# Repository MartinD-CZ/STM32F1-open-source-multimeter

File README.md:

# STM32 OpenSource Multimeter
*see the article [here](http://embedblog.eu/?p=438) or the video [here](https://youtu.be/qQX5iS70-mg)*

## Specs (revision 1.5 - latest stable)
1. voltage measurement: ±60 V, ±6 V, ±600 mV, ±60 m ranges, with DC or RMS data acquisition
2. current measurement: ±250 or ±2500 mA ranges, again with DC or RMS
3. can measure voltage and current simultaneously and display the product, ie power
4. measures continuity and displays the resistance and voltage drop
5. can perform simple component testing
6. frequency measurement up to 10 MHz

Additional features: isolated USB serial port; ; 2 kB EEPROM; 4 bit expansion port; battery voltage measurement & charging via USB; firmware update via USB; integrated kickstand; hold function

*Note: when this project started, it used STM32F1. Now it uses STM32F3, but I cannot rename the repository, so I hope it won't mislead anyone.*

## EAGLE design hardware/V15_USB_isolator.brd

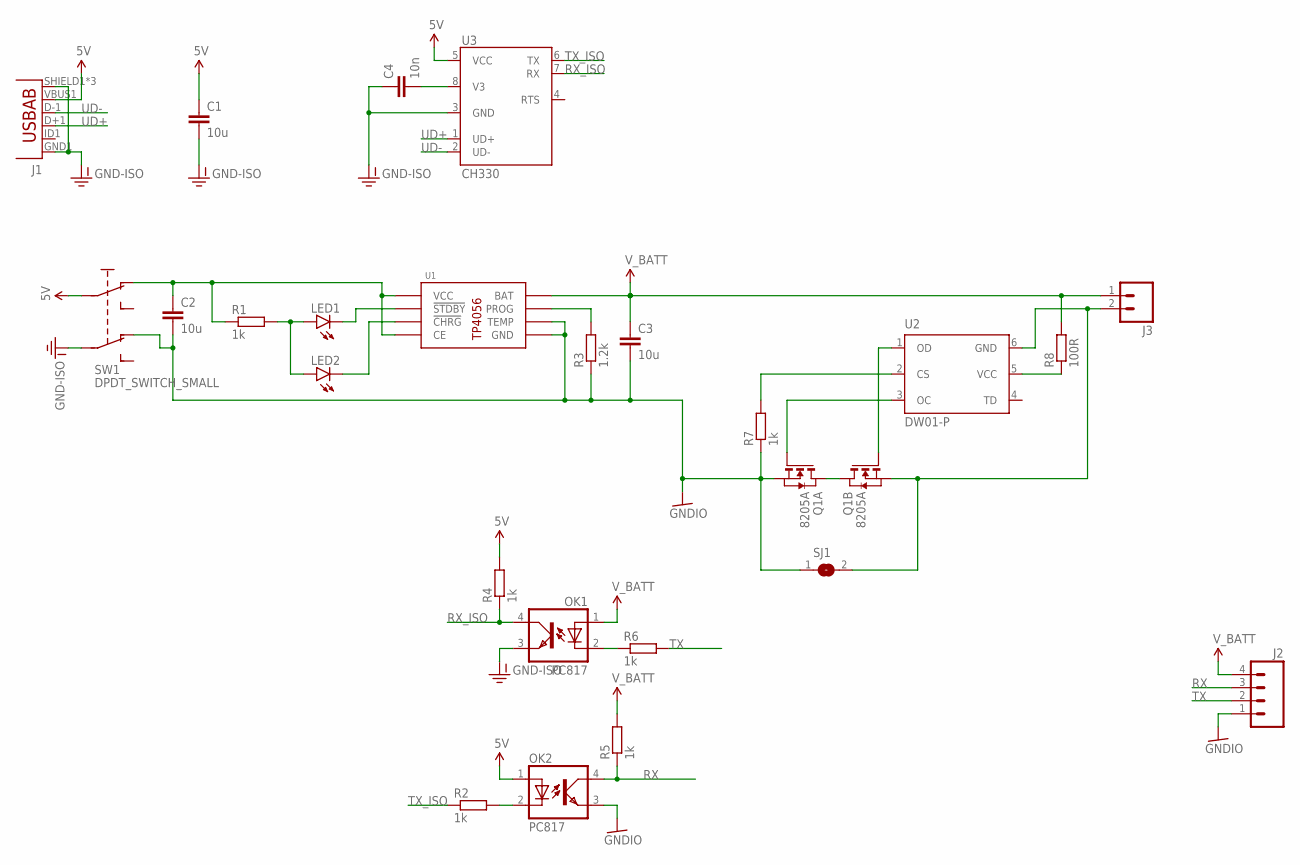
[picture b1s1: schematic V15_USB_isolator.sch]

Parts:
C1, C2, C3: 10u; C1206
C4: 10n; C1206
J1: USB-ABCONN-11794; USB-AB-MICRO-SMD_V03
J2: M04PTH; 1X04@1
J3: M02PTH3; 1X02_LONGPADS
LED1, LED2: LED1206-BOTTOM; LED-1206-BOTTOM
OK1, OK2: PC817; DIL04
Q1: 8205A; TSSOP8
R1, R2, R4, R5, R6, R7: 1k; R1206
R3: 1.2k; R1206
R8: 100R; R1206
SJ1: SJ
SW1: DPDT_SWITCH_SMALL; DPDT_SMALL
U1: TP4056; SOP8
U2: DW01-P; SOT23-6L
U3: CH330; SO08

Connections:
5V: C1.1, J1.VBUS1 (VBUS), OK2.1 (A), R4.2, SW1.P$2 (I1), U3.5 (VCC)
5V_ISO: C2.1, R1.1, SW1.P$1 (NC1), U1.4 (VCC), U1.8 (CE)
GND-ISO: C1.2, C4.1, J1.GND1 (GND), J1.SHIELD1 (SHIELD), J1.SHIELD2 (SHIELD), J1.SHIELD3 (SHIELD), OK1.3 (EMIT), SW1.P$5 (I2), U3.3 (GND)
GNDIO: C2.2, C3.2, J2.1, OK2.3 (EMIT), Q1.2 (S), Q1.3 (S), R3.1, R7.1, SJ1.1, SW1.P$6 (NC2), U1.1 (TEMP), U1.3 (GND)
unnamed: C4.2, U3.8 (V3)
unnamed: Q1.1 (D), Q1.8 (D)
unnamed: LED1.A, LED2.A, R1.2
unnamed: LED1.C, U1.6 (!STDBY)
unnamed: LED2.C, U1.7 (!CHRG)
unnamed: R3.2, U1.2 (PROG)
unnamed: OK2.2 (C), R2.2
unnamed: OK1.2 (C), R6.1
unnamed: R8.1, U2.5 (VCC)
unnamed: J3.2, Q1.6 (S), Q1.7 (S), SJ1.2, U2.6 (GND)
unnamed: Q1.5 (G), U2.1 (OD)
unnamed: Q1.4 (G), U2.3 (OC)
unnamed: R7.2, U2.2 (CS)
RX: J2.3, OK2.4 (COL), R5.1
RX_ISO: OK1.4 (COL), R4.1, U3.7 (RX)
TX: J2.2, R6.2
TX_ISO: R2.1, U3.6 (TX)
UD+: J1.D+1 (D+), U3.1 (UD+)
UD-: J1.D-1 (D-), U3.2 (UD-)
V_BATT: C3.1, J2.4, J3.1, OK1.1 (A), R5.2, R8.2, U1.5 (BAT)

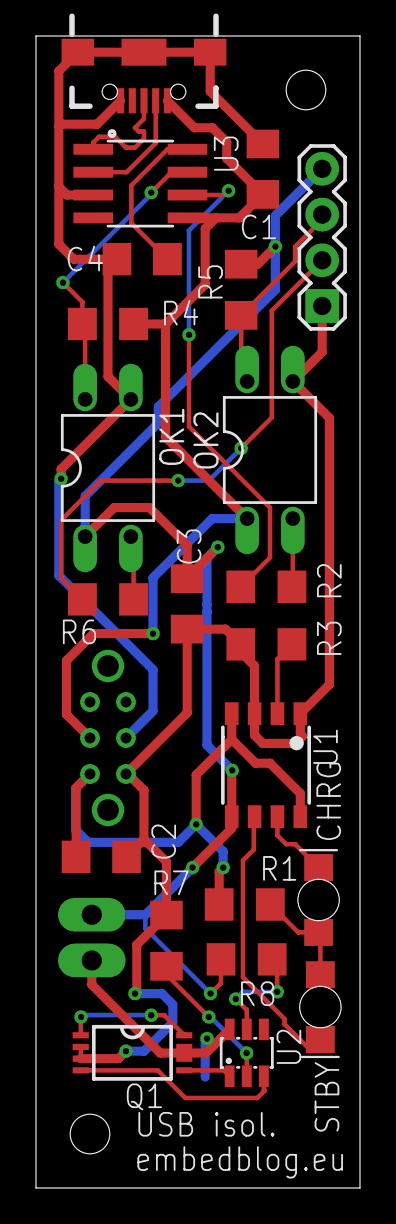
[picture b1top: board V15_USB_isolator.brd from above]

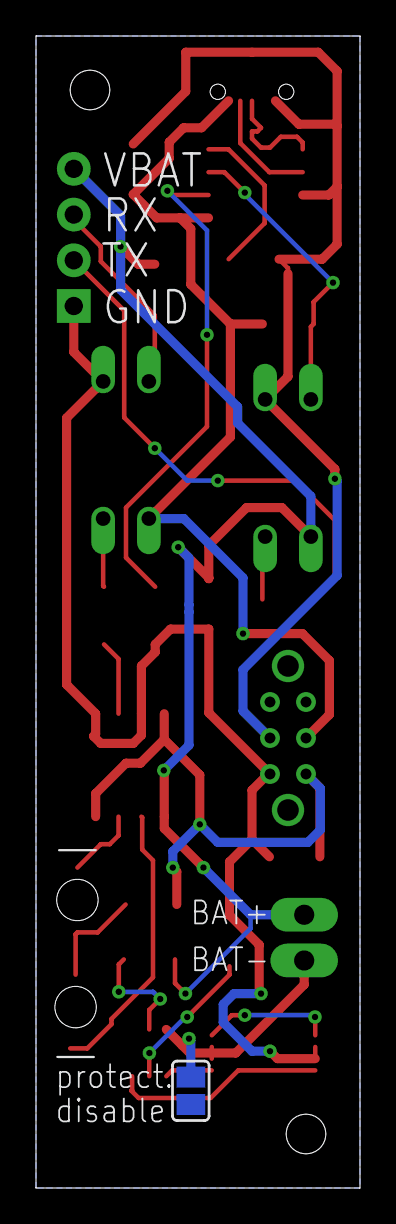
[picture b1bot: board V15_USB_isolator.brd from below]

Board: 2 copper layers, 18.0 x 64.0 mm, 25 parts (2 on the bottom side), 24 nets.

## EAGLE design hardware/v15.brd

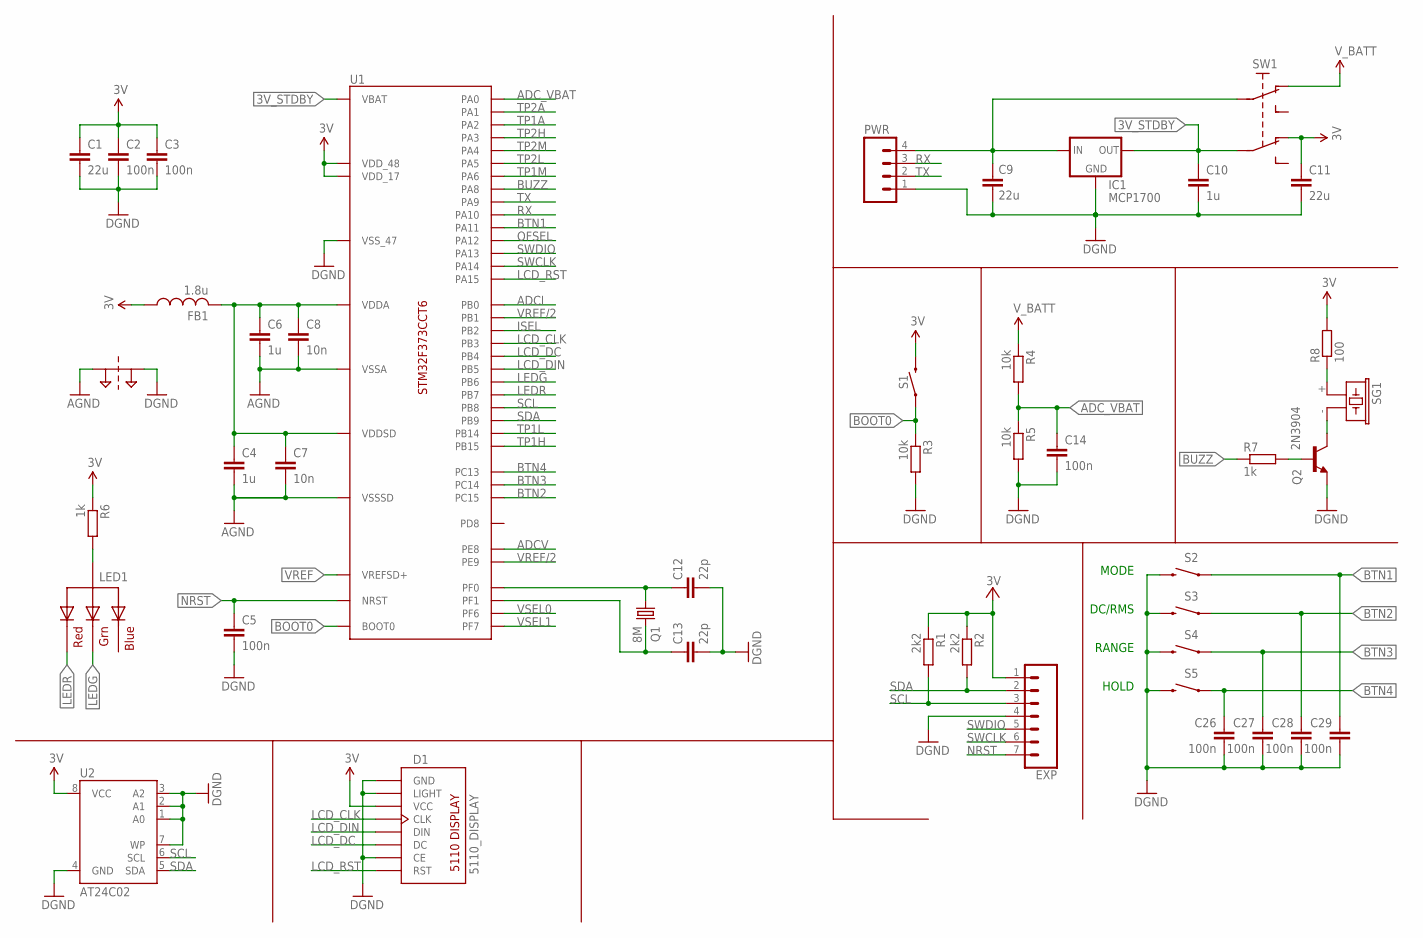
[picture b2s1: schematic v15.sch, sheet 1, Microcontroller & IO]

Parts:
C1, C9, C11: 22u; C1206
C2, C3, C5, C14, C26, C27, C28, C29: 100n; C1206
C4, C6, C10: 1u; C1206
C7, C8: 10n; C1206
C12, C13: 22p; C1206
D1: 5110_DISPLAY; 5110_LAYOUT
EXP: CONN_07; 1X07
FB1: 1.8u; 1206
IC1: MCP1700; SOT23
LED1: RGBLED_CA-5MM; LED5MMRGB
PT1: 2PT_GND_TIE
PWR: M04PTH; 1X04@1
Q1: 8M; HC49U-V
Q2: 2N3904; SOT23
R1, R2: 2k2; R1206
R3, R4, R5: 10k; R1206
R6, R7: 1k; R1206
R8: 100; R1206
S1: MOMENTARY-SWITCH-SPST-PTH-6.0MM; TACTILE_SWITCH_PTH_6.0MM
S2, S3, S4, S5: MOMENTARY-SWITCH-SPST-SMD-12MM; TACTILE_SWITCH_SMD_12MM
SG1: F/CM12P
SW1: DPDT_SWITCH_SMALL; DPDT_SMALL
U1: STM32F373CCT6; LQFP-48
U2: AT24C02; SOIC8

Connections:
3V: C1.1, C2.1, C3.1, C11.1, D1.VCC, EXP.1, FB1.1, R1.1, R2.1, R6.1, R8.2, S1.3 (2), SW1.P$6 (NC2), U1.17 (VDD_17), U1.48 (VDD_48), U2.8 (VCC); also elsewhere on the board
3V_STDBY: C10.1, IC1.2 (OUT), SW1.P$5 (I2), U1.1 (VBAT)
ADCI: U1.18 (PB0); also elsewhere on the board
ADCV: U1.21 (PE8); also elsewhere on the board
ADC_VBAT: C14.1, R4.2, R5.1, U1.10 (PA0)
AGND: C4.2, C6.2, C7.2, C8.2, PT1.P$1, U1.8 (VSSA), U1.23 (VSSSD); also elsewhere on the board
BOOT0: R3.1, S1.1, U1.44 (BOOT0)
BTN1: C29.1, S2.1, U1.32 (PA11)
BTN2: C28.1, S3.1, U1.4 (PC15)
BTN3: C27.1, S4.1, U1.3 (PC14)
BTN4: C26.1, S5.1, U1.2 (PC13)
BUZZ: R7.1, U1.29 (PA8)
GND: C1.2, C2.2, C3.2, C5.2, C9.2, C10.2, C11.2, C12.2, C13.2, C14.2, C26.2, C27.2, C28.2, C29.2, D1.CE, D1.GND, D1.LIGHT, EXP.4, IC1.1 (GND), PT1.P$2, PWR.1, Q2.2 (E), R3.2, R5.2, S2.3 (2), S3.3 (2), S4.3 (2), S5.3 (2), U1.47 (VSS_47), U2.1 (A0), U2.2 (A1), U2.3 (A2), U2.4 (GND), U2.7 (WP)
ISEL: U1.20 (PB2); also elsewhere on the board
LCD_CLK: D1.CLK, U1.39 (PB3)
LCD_DC: D1.DC, U1.40 (PB4)
LCD_DIN: D1.DIN, U1.41 (PB5)
LCD_RST: D1.RST, U1.38 (PA15)
LEDG: LED1.3 (GREEN), U1.42 (PB6)
LEDR: LED1.1 (RED), U1.43 (PB7)
unnamed: C12.1, Q1.1, U1.5 (PF0)
unnamed: C4.1, C6.1, C7.1, C8.1, FB1.2, U1.9 (VDDA), U1.24 (VDDSD)
unnamed: C9.1, IC1.3 (IN), PWR.4, SW1.P$2 (I1)
unnamed: LED1.2 (VCC), R6.2
unnamed: R8.1, SG1.+ (1)
unnamed: C13.1, Q1.2, U1.6 (PF1)
unnamed: Q2.3 (C), SG1.- (2)
unnamed: Q2.1 (B), R7.2
NRST: C5.1, EXP.7, U1.7 (NRST)
OFSEL: U1.33 (PA12); also elsewhere on the board
RX: PWR.3, U1.31 (PA10)
SCL: EXP.3, R1.2, U1.45 (PB8), U2.6 (SCL)
SDA: EXP.2, R2.2, U1.46 (PB9), U2.5 (SDA)
SWCLK: EXP.6, U1.37 (PA14)
SWDIO: EXP.5, U1.34 (PA13)
TP1A: U1.12 (PA2); also elsewhere on the board
TP1H: U1.27 (PB15); also elsewhere on the board
TP1L: U1.26 (PB14); also elsewhere on the board
TP1M: U1.16 (PA6); also elsewhere on the board
TP2A: U1.11 (PA1); also elsewhere on the board
TP2H: U1.13 (PA3); also elsewhere on the board
TP2L: U1.15 (PA5); also elsewhere on the board
TP2M: U1.14 (PA4); also elsewhere on the board
TX: PWR.2, U1.30 (PA9)
VREF: U1.25 (VREFSD+); also elsewhere on the board
VREF/2: U1.19 (PB1), U1.22 (PE9); also elsewhere on the board
VSEL0: U1.35 (PF6); also elsewhere on the board
VSEL1: U1.36 (PF7); also elsewhere on the board
V_BATT: R4.1, SW1.P$1 (NC1)

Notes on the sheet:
MODE
RANGE
DC/RMS
HOLD

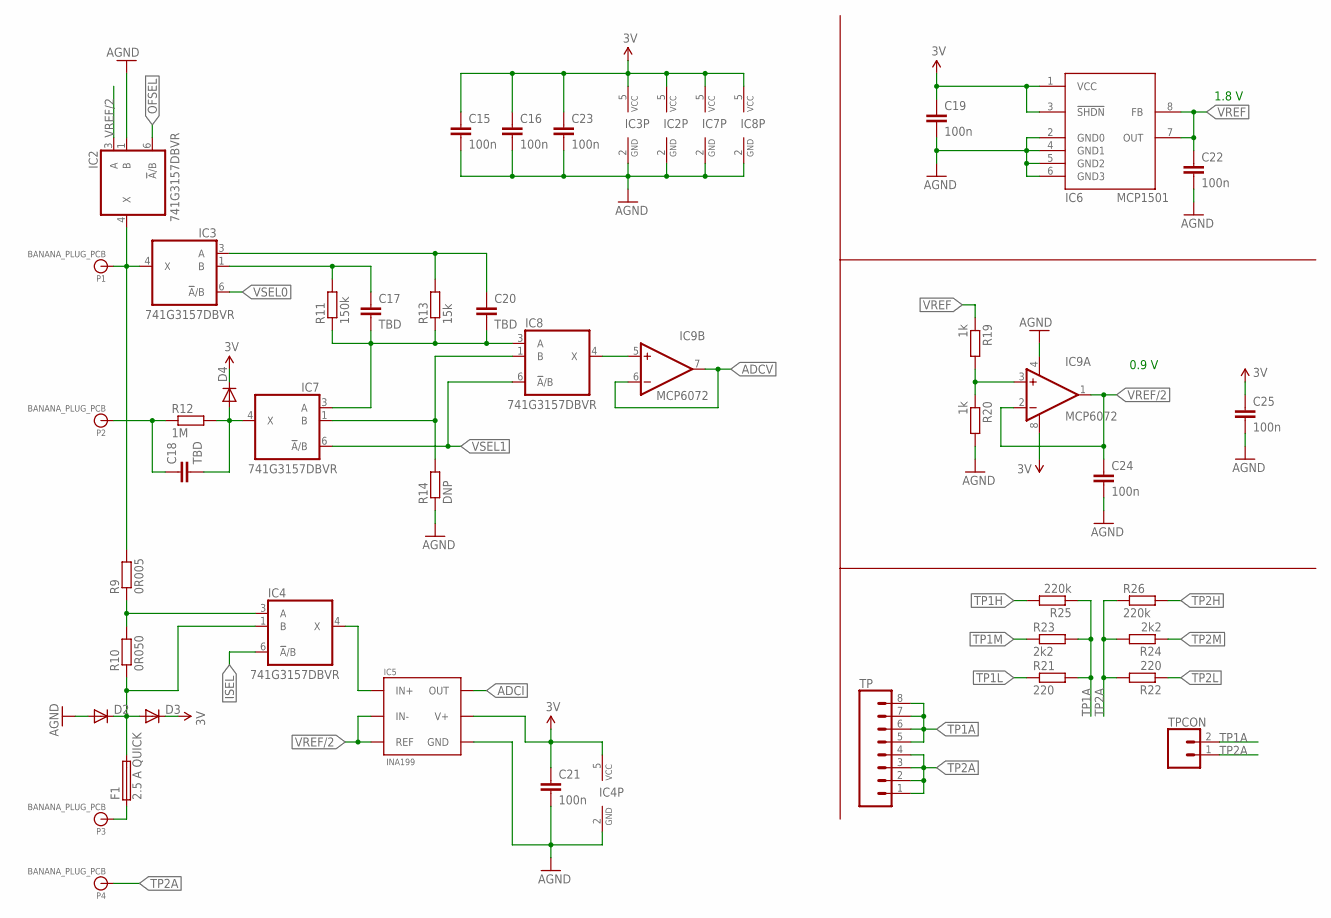
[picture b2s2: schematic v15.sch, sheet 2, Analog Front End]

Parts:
C15, C16, C21, C23: 100n; 1206
C17, C18, C20: TBD; 1206
C19, C22, C24, C25: 100n; C1206
D2, D3, D4: DIODE-MINIMELF; MINIMELF
F1: 2.5 A QUICK; SHK20L
IC2, IC3, IC4, IC7, IC8: 741G3157DBVR; DBV_R-PDSO-G6
IC5: INA199; SC70-6
IC6: MCP1501; SO08
IC9: MCP6072; SO08
P1, P2, P3, P4: BANANA_PLUG_PCB; BANANA_6MMHOLE
R9: 0R005; R1206
R10: 0R050; R1206
R11: 150k; R1206
R12: 1M; R1206
R13: 15k; R1206
R14: DNP; R1206
R19, R20: 1k; R1206
R21, R22: 220; R1206
R23, R24: 2k2; R1206
R25, R26: 220k; R1206
TP: CONN_08SMD-STRAIGHT-FEMALE; 1X08_SMD
TPCON: CONN_02; 1X02

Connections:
3V: C15.1, C16.1, C19.1, C21.1, C23.1, C25.1, D3.C, D4.C, IC2.5 (VCC), IC3.5 (VCC), IC4.5 (VCC), IC5.3 (V+), IC6.1 (VCC), IC6.3 (!SHDN), IC7.5 (VCC), IC8.5 (VCC), IC9.8 (V+); also elsewhere on the board
ADCI: IC5.6 (OUT); also elsewhere on the board
ADCV: IC9.6 (-IN), IC9.7 (OUT); also elsewhere on the board
AGND: C15.2, C16.2, C19.2, C21.2, C22.2, C23.2, C24.2, C25.2, D2.A, IC2.1 (B), IC2.2 (GND), IC3.2 (GND), IC4.2 (GND), IC5.2 (GND), IC6.2 (GND0), IC6.4 (GND1), IC6.5 (GND2), IC6.6 (GND3), IC7.2 (GND), IC8.2 (GND), IC9.4 (V-), R14.1, R20.2; also elsewhere on the board
COM: IC2.4 (X), IC3.4 (X), P1.P$1, R9.2
ISEL: IC4.6 (!A!/B); also elsewhere on the board
unnamed: C18.1, P2.P$1, R12.1
unnamed: C17.1, IC3.1 (B), R11.2
unnamed: C20.1, IC3.3 (A), R13.2
unnamed: C18.2, D4.A, IC7.4 (X), R12.2
unnamed: IC4.3 (A), R9.1, R10.2
unnamed: C17.2, C20.2, IC7.3 (A), IC8.3 (A), R11.1, R13.1
unnamed: D2.C, D3.A, F1.2A (2), IC4.1 (B), R10.1
unnamed: IC8.4 (X), IC9.5 (+IN)
unnamed: IC7.1 (B), IC8.1 (B), R14.2
unnamed: IC9.3 (+IN), R19.2, R20.1
unnamed: IC4.4 (X), IC5.4 (IN+)
unnamed: F1.1A (1), P3.P$1
OFSEL: IC2.6 (!A!/B); also elsewhere on the board
TP1A: R21.2, R23.2, R25.1, TP.5, TP.6, TP.7, TP.8, TPCON.2; also elsewhere on the board
TP1H: R25.2; also elsewhere on the board
TP1L: R21.1; also elsewhere on the board
TP1M: R23.1; also elsewhere on the board
TP2A: P4.P$1, R22.2, R24.2, R26.1, TP.1, TP.2, TP.3, TP.4, TPCON.1; also elsewhere on the board
TP2H: R26.2; also elsewhere on the board
TP2L: R22.1; also elsewhere on the board
TP2M: R24.1; also elsewhere on the board
VREF: C22.1, IC6.7 (OUT), IC6.8 (FB), R19.1; also elsewhere on the board
VREF/2: C24.1, IC2.3 (A), IC5.1 (REF), IC5.5 (IN-), IC9.1 (OUT), IC9.2 (-IN); also elsewhere on the board
VSEL0: IC3.6 (!A!/B); also elsewhere on the board
VSEL1: IC7.6 (!A!/B), IC8.6 (!A!/B); also elsewhere on the board

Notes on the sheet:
1.8 V
0.9 V

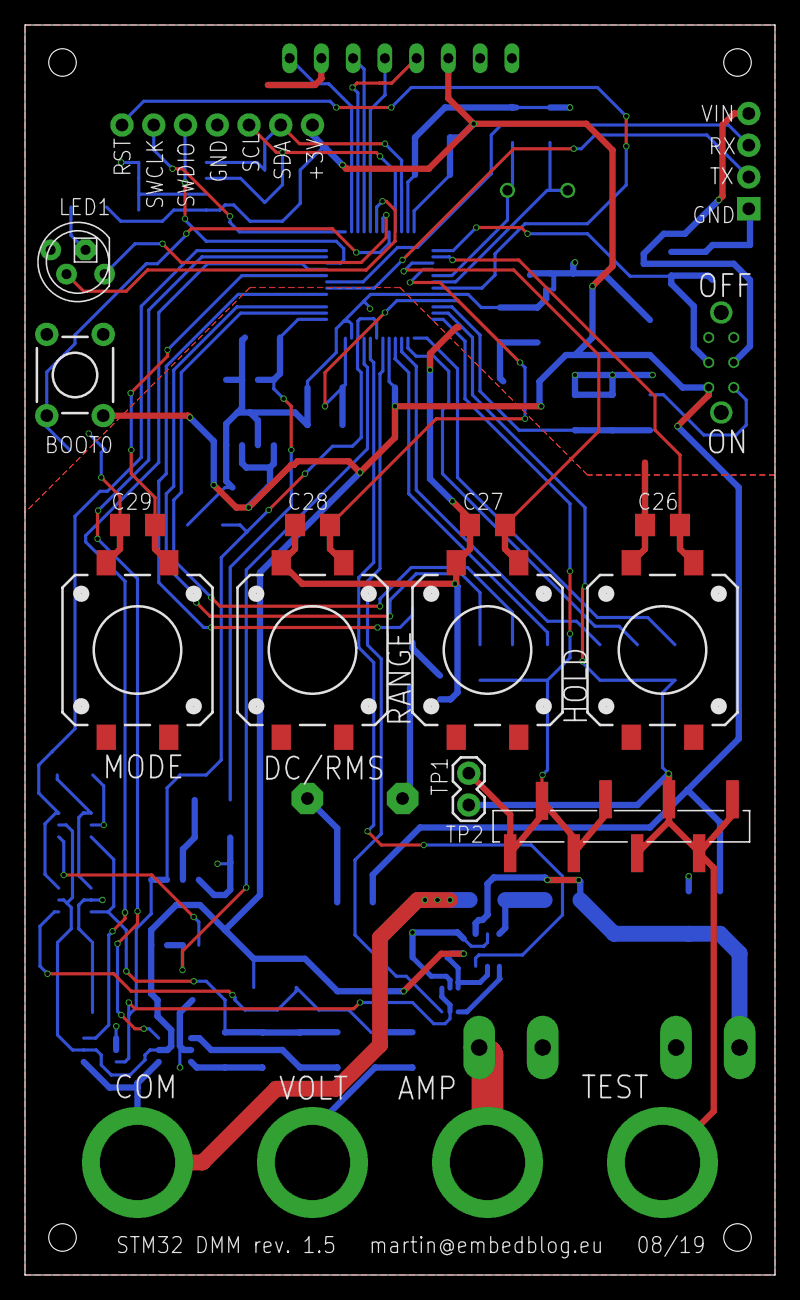
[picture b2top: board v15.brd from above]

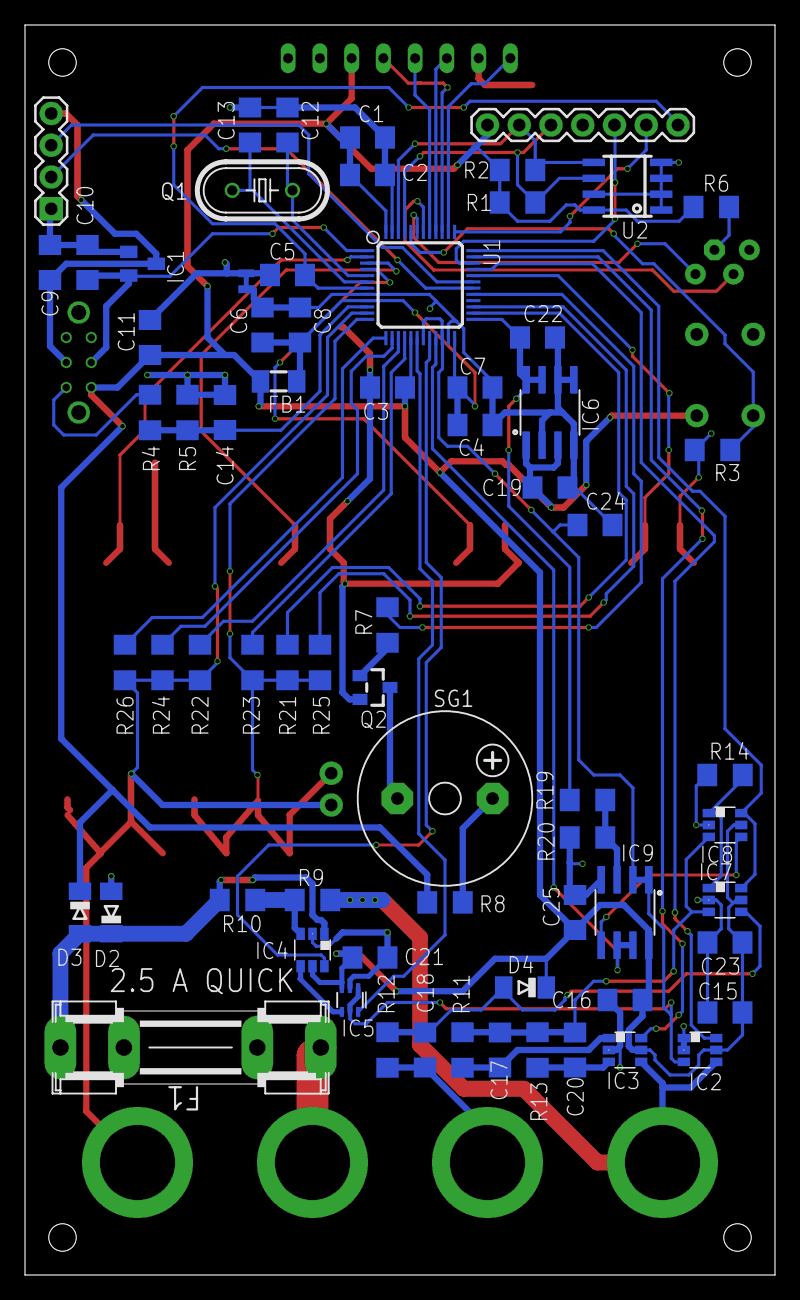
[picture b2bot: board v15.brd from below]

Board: 2 copper layers, 60.0 x 100.0 mm, 87 parts (69 on the bottom side), 62 nets.

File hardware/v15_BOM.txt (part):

Part  Value                           Device                          Package                  Description                                                                                                     MF MPN OC_FARNELL OC_NEWARK PROD_ID     SF_ID     SF_SKU   
C1    22u                             C-EUC1206                       C1206                    CAPACITOR, European symbol                                                                                                                                                 
C2    100n                            C-EUC1206                       C1206                    CAPACITOR, European symbol                                                                                                                                                 
C3    100n                            C-EUC1206                       C1206                    CAPACITOR, European symbol                                                                                                                                                 
C4    1u                              C-EUC1206                       C1206                    CAPACITOR, European symbol                                                                                                                                                 
C5    100n                            C-EUC1206                       C1206                    CAPACITOR, European symbol                                                                                                                                                 
C6    1u                              C-EUC1206                       C1206                    CAPACITOR, European symbol                                                                                                                                                 
C7    10n                             C-EUC1206                       C1206                    CAPACITOR, European symbol                                                                                                                                                 
C8    10n                             C-EUC1206                       C1206                    CAPACITOR, European symbol                                                                                                                                                 
C9    22u                             C-EUC1206                       C1206                    CAPACITOR, European symbol                                                                                                                                                 
C10   1u                              C-EUC1206                       C1206                    CAPACITOR, European symbol                                                                                                                                                 
C11   22u                             C-EUC1206                       C1206                    CAPACITOR, European symbol                                                                                                                                                 
C12   22p                             C-EUC1206                       C1206                    CAPACITOR, European symbol                                                                                                                                                 
C13   22p                             C-EUC1206                       C1206                    CAPACITOR, European symbol                                                                                                                                                 
C14   100n                            C-EUC1206                       C1206                    CAPACITOR, European symbol                                                                                                                                                 
C15   100n                            CAP1206                         1206                     Capacitor                                                                                                                                                                  
C16   100n                            CAP1206                         1206                     Capacitor                                                                                                                                                                  
C17   TBD                             CAP1206                         1206                     Capacitor                                                                                                                                                                  
C18   TBD                             CAP1206                         1206                     Capacitor                                                                                                                                                                  
C19   100n                            C-EUC1206                       C1206                    CAPACITOR, European symbol                                                                                                                                                 
C20   TBD                             CAP1206                         1206                     Capacitor                                                                                                                                                                  
C21   100n                            CAP1206                         1206                     Capacitor                                                                                                                                                                  
C22   100n                            C-EUC1206                       C1206                    CAPACITOR, European symbol                                                                                                                                                 
C23   100n                            CAP1206                         1206                     Capacitor                                                                                                                                                                  
C24   100n                            C-EUC1206                       C1206                    CAPACITOR, European symbol                                                                                                                                                 
C25   100n                            C-EUC1206                       C1206                    CAPACITOR, European symbol                                                                                                                                                 
C26   100n                            C-EUC1206                       C1206                    CAPACITOR, European symbol                                                                                                                                                 
C27   100n                            C-EUC1206                       C1206                    CAPACITOR, European symbol                                                                                                                                                 
C28   100n                            C-EUC1206                       C1206                    CAPACITOR, European symbol                                                                                                                                                 
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
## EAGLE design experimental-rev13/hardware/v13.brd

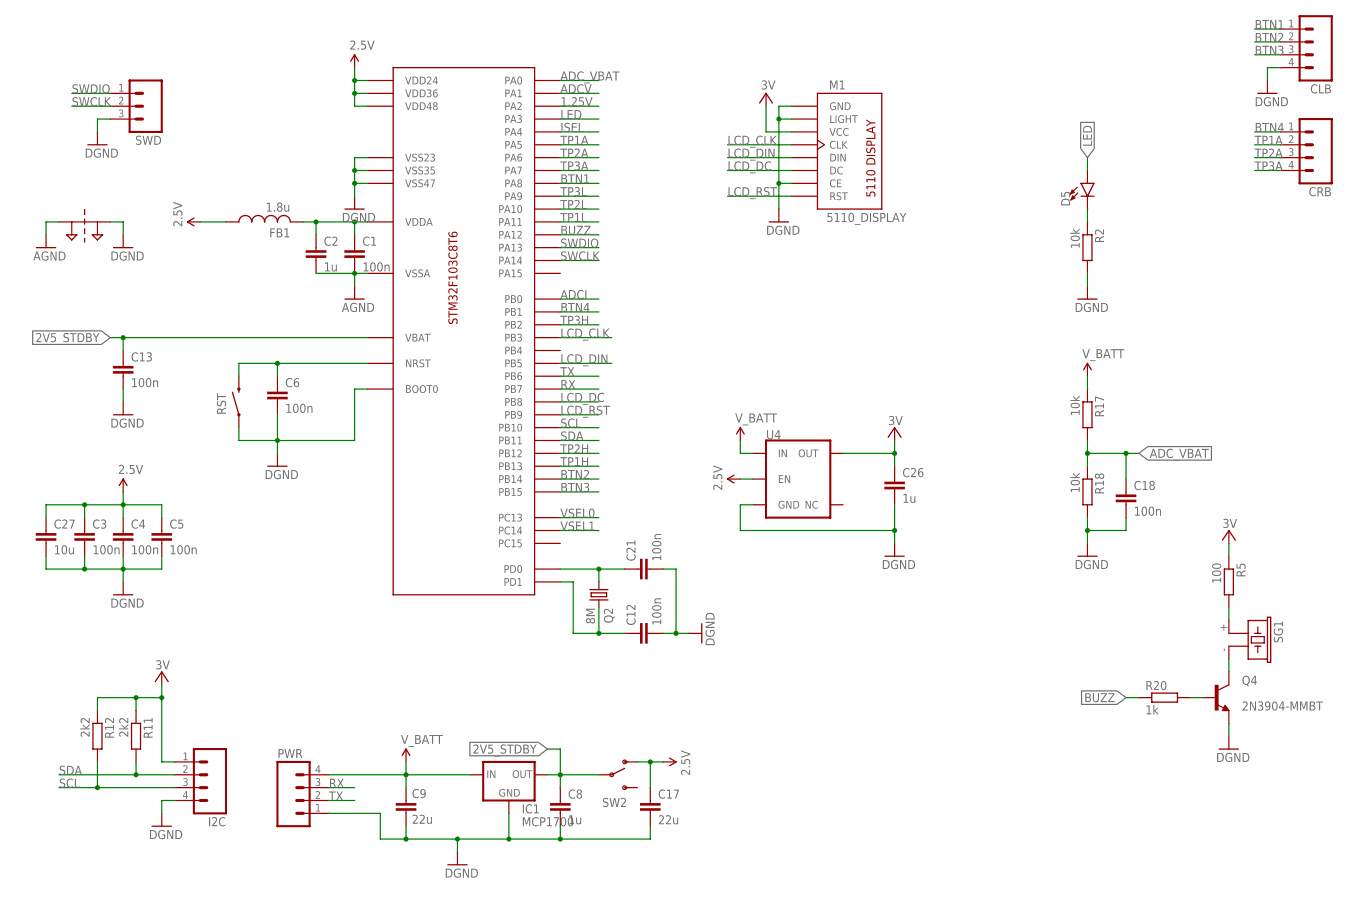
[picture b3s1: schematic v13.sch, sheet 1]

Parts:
C1, C3, C4, C5, C6, C12, C13, C18, C21: 100n; C1206
C2, C8, C26: 1u; C1206
C9, C17: 22u; C1206
C27: 10u; C1206
CLB: M04PTH; 1X04@1
CRB: M04PTH; 1X04@1
D5: LED1206; LED-1206
FB1: 1.8u; 1206
I2C: M04PTH; 1X04@1
IC1: MCP1700; SOT23
M1: 5110_DISPLAY; 5110_LAYOUT
PWR: M04PTH; 1X04@1
Q2: 8M; HC49U-V
Q4: 2N3904-MMBT; SOT23
R2, R17, R18: 10k; R1206
R5: 100; R1206
R11, R12: 2k2; R1206
R20: 1k; R1206
RST: SWITCH-MOMENTARY-2SMD; TACTILE-SWITCH-SMD
SG1: F/CM12P
SJ1: 2PT_GND_TIE
SW2: SK-12D07; SK12SWITCH
SWD: M03PTH; 1X03
U4: 3.3V; SOT23-5
U$1: STM32F103C8T6; TQFP-48

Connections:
1.25V: U$1.12 (PA2); also elsewhere on the board
2.5V: C3.1, C4.1, C5.1, C17.1, C27.1, FB1.1, SW2.IN (O), U4.3 (EN), U$1.24 (VDD24), U$1.36 (VDD36), U$1.48 (VDD48); also elsewhere on the board
2V5_STDBY: C8.1, C13.1, IC1.2 (OUT), SW2.P1, U$1.1 (VBAT)
3V: C26.1, I2C.1, M1.VCC, R5.1, R11.1, R12.1, U4.5 (OUT); also elsewhere on the board
ADCI: U$1.18 (PB0); also elsewhere on the board
ADCV: U$1.11 (PA1); also elsewhere on the board
ADC_VBAT: C18.1, R17.2, R18.1, U$1.10 (PA0)
AGND: C1.2, C2.2, SJ1.P$1, U$1.8 (VSSA); also elsewhere on the board
BTN1: CLB.1, U$1.29 (PA8)
BTN2: CLB.2, U$1.27 (PB14)
BTN3: CLB.3, U$1.28 (PB15)
BTN4: CRB.1, U$1.19 (PB1)
BUZZ: R20.1, U$1.33 (PA12)
GND: C3.2, C4.2, C5.2, C6.2, C8.2, C9.2, C12.2, C13.2, C17.2, C18.2, C21.2, C26.2, C27.2, CLB.4, I2C.4, IC1.1 (GND), M1.CE, M1.GND, M1.LIGHT, PWR.1, Q4.2 (E), R2.2, R18.2, RST.1, SJ1.P$2, SWD.3, U4.2 (GND), U$1.23 (VSS23), U$1.35 (VSS35), U$1.44 (BOOT0), U$1.47 (VSS47); also elsewhere on the board
ISEL: U$1.14 (PA4); also elsewhere on the board
LCD_CLK: M1.CLK, U$1.39 (PB3)
LCD_DC: M1.DC, U$1.45 (PB8)
LCD_DIN: M1.DIN, U$1.41 (PB5)
LCD_RST: M1.RST, U$1.46 (PB9)
LED: D5.A, U$1.13 (PA3)
unnamed: C6.1, RST.3 (2), U$1.7 (NRST)
unnamed: C21.1, Q2.1, U$1.5 (PD0)
unnamed: C1.1, C2.1, FB1.2, U$1.9 (VDDA)
unnamed: D5.C, R2.1
unnamed: R5.2, SG1.+ (1)
unnamed: C12.1, Q2.2, U$1.6 (PD1)
unnamed: Q4.3 (C), SG1.- (2)
unnamed: Q4.1 (B), R20.2
RX: PWR.3, U$1.43 (PB7)
SCL: I2C.3, R12.2, U$1.21 (PB10)
SDA: I2C.2, R11.2, U$1.22 (PB11)
SWCLK: SWD.2, U$1.37 (PA14)
SWDIO: SWD.1, U$1.34 (PA13)
TP1A: CRB.2, U$1.15 (PA5); also elsewhere on the board
TP1H: U$1.26 (PB13); also elsewhere on the board
TP1L: U$1.32 (PA11); also elsewhere on the board
TP2A: CRB.3, U$1.16 (PA6); also elsewhere on the board
TP2H: U$1.25 (PB12); also elsewhere on the board
TP2L: U$1.31 (PA10); also elsewhere on the board
TP3A: CRB.4, U$1.17 (PA7); also elsewhere on the board
TP3H: U$1.20 (PB2); also elsewhere on the board
TP3L: U$1.30 (PA9); also elsewhere on the board
TX: PWR.2, U$1.42 (PB6)
VSEL0: U$1.2 (PC13); also elsewhere on the board
VSEL1: U$1.3 (PC14); also elsewhere on the board
V_BATT: C9.1, IC1.3 (IN), PWR.4, R17.1, U4.1 (IN); also elsewhere on the board

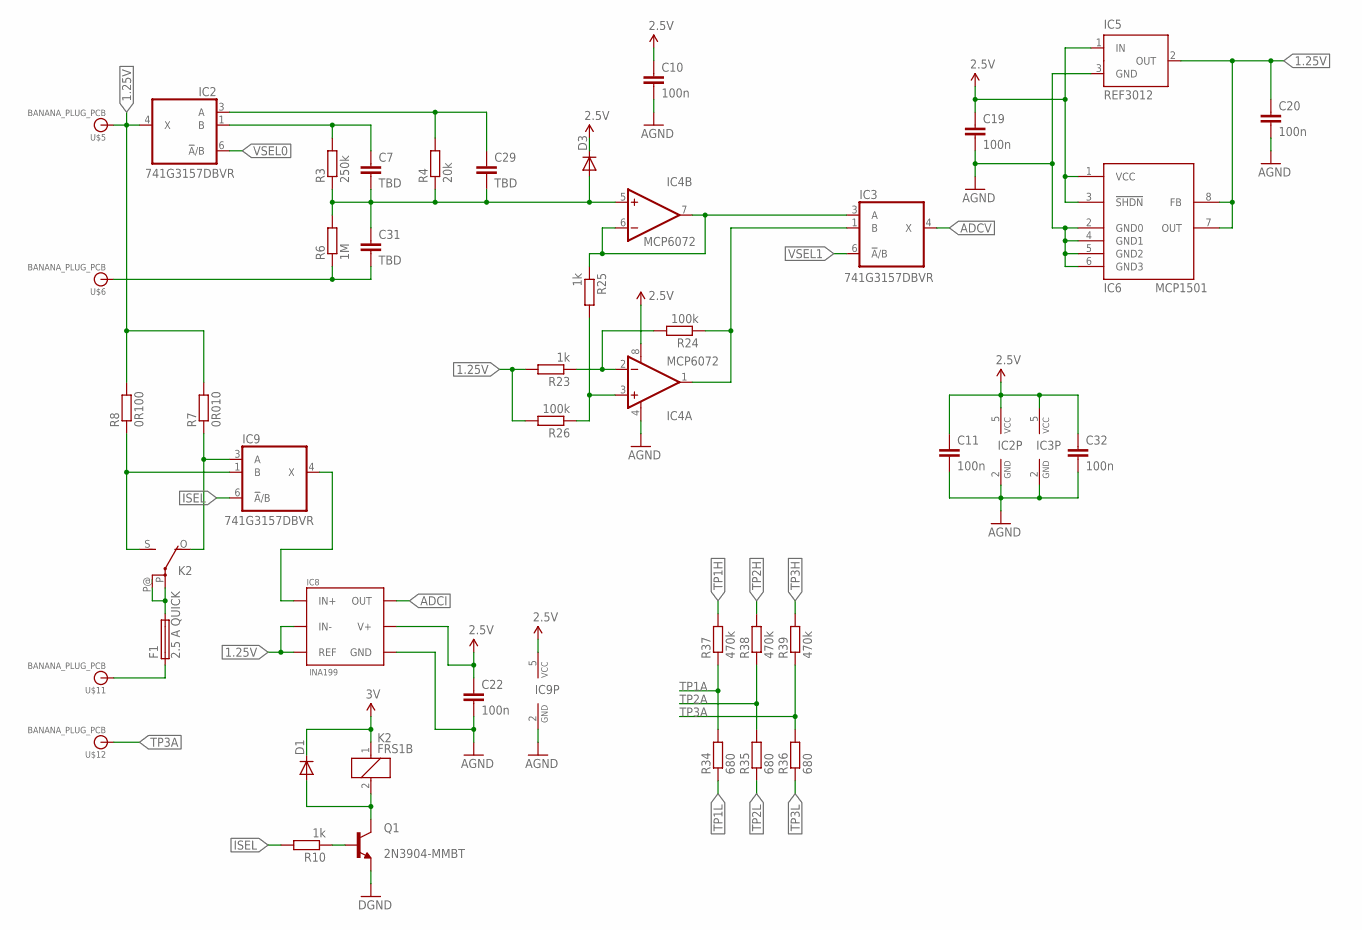
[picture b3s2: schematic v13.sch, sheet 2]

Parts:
C7, C29, C31: TBD; 1206
C10, C11, C22, C32: 100n; 1206
C19, C20: 100n; C1206
D1, D3: DIODE-MINIMELF; MINIMELF
F1: 2.5 A QUICK; SHK20L
IC2, IC3, IC9: 741G3157DBVR; DBV_R-PDSO-G6
IC4: MCP6072; SO08
IC5: REF3012; SOT23
IC6: MCP1501; SO08
IC8: INA199; SC70-6
K2: FRS1B
Q1: 2N3904-MMBT; SOT23
R3: 250k; R1206
R4: 20k; R1206
R6: 1M; R1206
R7: 0R010; R1206
R8: 0R100; R1206
R10, R23, R25: 1k; R1206
R24, R26: 100k; R1206
R34, R35, R36: 680; R1206
R37, R38, R39: 470k; R1206
U$5, U$6, U$11, U$12: BANANA_PLUG_PCB; BANANA_6MMHOLE

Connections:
1.25V: C20.1, IC2.4 (X), IC5.2 (OUT), IC6.7 (OUT), IC6.8 (FB), IC8.1 (REF), IC8.5 (IN-), R7.2, R8.2, R23.2, R26.2, U$5.P$1; also elsewhere on the board
2.5V: C10.1, C11.1, C19.1, C22.1, C32.1, D3.C, IC2.5 (VCC), IC3.5 (VCC), IC4.8 (V+), IC5.1 (IN), IC6.1 (VCC), IC6.3 (!SHDN), IC8.3 (V+), IC9.5 (VCC); also elsewhere on the board
3V: D1.C, K2.1; also elsewhere on the board
ADCI: IC8.6 (OUT); also elsewhere on the board
ADCV: IC3.4 (X); also elsewhere on the board
AGND: C10.2, C11.2, C19.2, C20.2, C22.2, C32.2, IC2.2 (GND), IC3.2 (GND), IC4.4 (V-), IC5.3 (GND), IC6.2 (GND0), IC6.4 (GND1), IC6.5 (GND2), IC6.6 (GND3), IC8.2 (GND), IC9.2 (GND); also elsewhere on the board
GND: Q1.2 (E); also elsewhere on the board
ISEL: IC9.6 (!A!/B), R10.2; also elsewhere on the board
unnamed: C7.1, IC2.1 (B), R3.2
unnamed: C29.1, IC2.3 (A), R4.2
unnamed: C7.2, C29.2, C31.1, D3.A, IC4.5 (+IN), R3.1, R4.1, R6.2
unnamed: Q1.1 (B), R10.1
unnamed: F1.2A (2), K2.P, K2.P@
unnamed: C31.2, R6.1, U$6.P$1
unnamed: IC9.1 (B), K2.S, R8.1
unnamed: D1.A, K2.2, Q1.3 (C)
unnamed: IC9.3 (A), K2.O, R7.1
unnamed: IC8.4 (IN+), IC9.4 (X)
unnamed: F1.1A (1), U$11.P$1
unnamed: IC3.1 (B), IC4.1 (OUT), R24.1
unnamed: IC4.2 (-IN), R23.1, R24.2
unnamed: IC4.3 (+IN), R25.2, R26.1
unnamed: IC3.3 (A), IC4.6 (-IN), IC4.7 (OUT), R25.1
TP1A: R34.2, R37.1; also elsewhere on the board
TP1H: R37.2; also elsewhere on the board
TP1L: R34.1; also elsewhere on the board
TP2A: R35.2, R38.1; also elsewhere on the board
TP2H: R38.2; also elsewhere on the board
TP2L: R35.1; also elsewhere on the board
TP3A: R36.2, R39.1, U$12.P$1; also elsewhere on the board
TP3H: R39.2; also elsewhere on the board
TP3L: R36.1; also elsewhere on the board
VSEL0: IC2.6 (!A!/B); also elsewhere on the board
VSEL1: IC3.6 (!A!/B); also elsewhere on the board

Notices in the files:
parts and their libraries:
SparkFun-Electromechanical: Licensing: Creative Commons ShareAlike 4.0 International - https://creativecommons.org/licenses/by-sa/4.0
m-pad-2.1: License : GNU General Public License version 2 (see bottom)
